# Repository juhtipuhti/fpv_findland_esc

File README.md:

# fpv_findland_esc
20x20mm mounted esc made for AM32. Currently work in progress. Confirmed to spin motors, but there are some emf problems at high output.

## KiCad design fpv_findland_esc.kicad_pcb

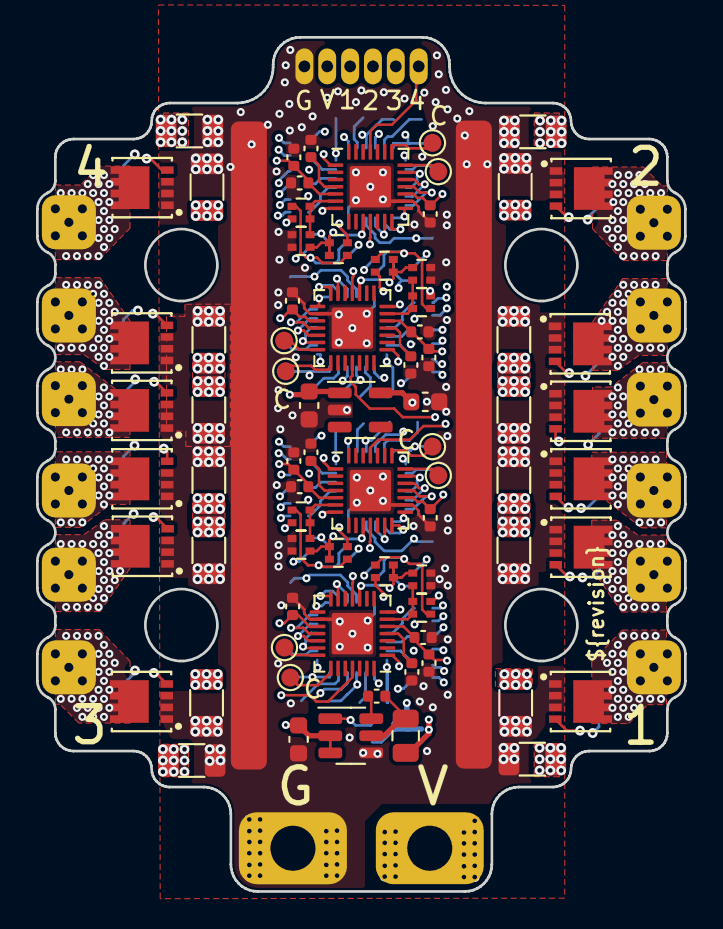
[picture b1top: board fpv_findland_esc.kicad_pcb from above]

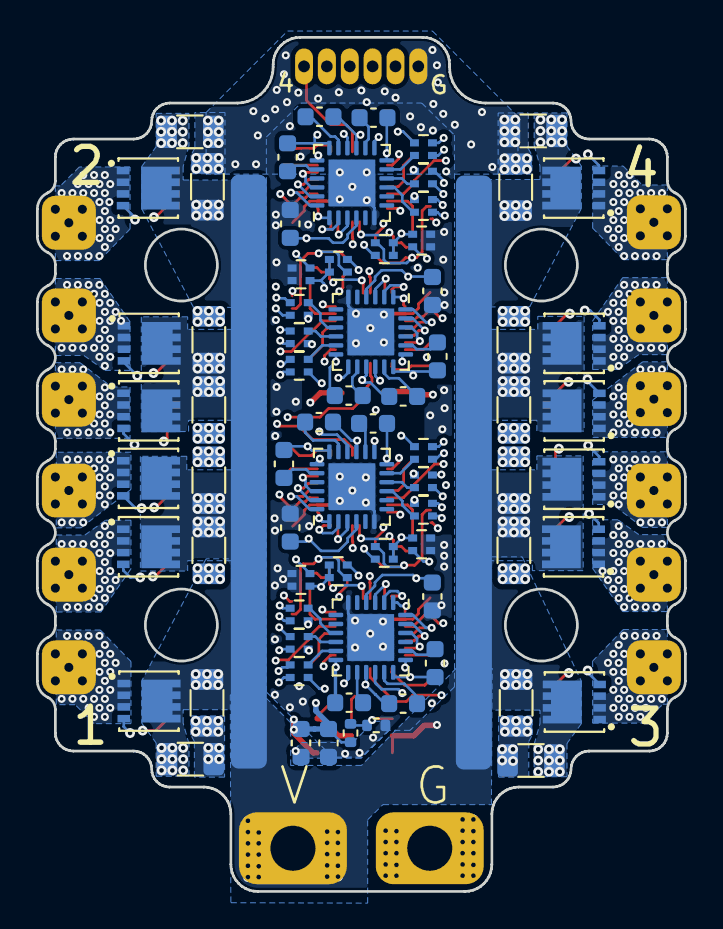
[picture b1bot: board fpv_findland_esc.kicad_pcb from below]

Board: 6 copper layers, 36.0 x 47.4 mm, 166 parts (74 on the bottom side), 139 nets.

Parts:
C1, C2, C6, C7, C8, C10, C11, C16, C24, C25, C26, C27, C29, C30, C31, C32, C33, C34, C35, C37, C39, C40, C41, C42, C43, C44, C47, C53, C60, C61, C63, C64: 10uF X7R; C_1206_Slim
C3, C4, C5, C12, C13, C14, C15, C19, C20, C21, C23, C28, C65: 100nF; C_0402_1005Metric
C9, C18, C69, C70: 1uF; C_0402_1005Metric
C17, C22, C38, C52, C59, C62, C66, C67, C68: 10uF; C_0603_1608Metric
C36, C45, C46, C48, C49, C50, C51, C54, C55, C56, C57, C58: 1uF; C_0603_1608Metric
J1, J3, J4, J5, J6, J7, J8, J9, J10, J11, J12, J13: Conn_01x01_Pin; MotorPad
J2: Conn_01x06; PadsHole_1x06_P1.27mm
L1: 10uF; C_0805_2012Metric
Q1, Q2, Q3, Q4, Q5, Q6, Q7, Q8, Q9, Q10, Q11, Q12, Q13, Q14, Q15, Q16, Q17, Q18, Q19, Q20, Q21, Q22, Q23, Q24: FDMC8010DC; TRANS_FDMC8010DC
R1: 20K; R_0402_1005Metric
R2: 230K; R_0402_1005Metric
RN1, RN2, RN3, RN4, RN5, RN6, RN7, RN8, RN9, RN10, RN11, RN12, RN13, RN14, RN15, RN16, RN20, RN22, RN24, RN25: 10K; R_Array_Slim_2x0402
RN17, RN18, RN19, RN21, RN23, RN26, RN27, RN28, RN29, RN30, RN31, RN32: 22R; R_Array_Slim_2x0402
TP1, TP2, TP3, TP5, TP6, TP7, TP8, TP10: TestPoint; TestPoint_Pad_D1.0mm
TP4, TP9: BussBar; 2mmBussBar36MM
TP11, TP12: BatteryPad
TP13, TP14: BussBar; 2mmBussBar33MM
U1, U3, U4, U6: GD32E230G8U6; QFN-28-1EP_4x4mm_P0.4mm_EP2.6x2.6mm
U2: WL2851E33; SOT-23-5
U5: AP63200; SOT-23-6
U7, U8, U9, U10: DRV8300D; QFN-24-1EP_4x4mm_P0.5mm_EP2.6x2.6mm

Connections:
/3.3V: C3.1, C5.1, C9.1, C12.1, C13.1, C14.1, C15.1, C18.1, C22.1, C23.1, C28.1, C69.1, C70.1, U1.5 (VDDA), U1.17 (VDD), U2.5 (VOUT), U3.5 (VDDA), U3.17 (VDD), U4.5 (VDDA), U4.17 (VDD), U6.5 (VDDA), U6.17 (VDD)
/5V: C17.1, C38.1, C52.1, C59.1, C62.1, C66.1, C67.1, L1.2, R2.1, U2.1 (VIN), U7.4 (VDD), U8.4 (VDD), U9.4 (VDD), U10.4 (VDD)
/ESC1/AHIGH: U4.20 (PA10), U8.22 (INHA)
/ESC1/ALOW: U4.15 (PB1), U8.1 (INLA)
/ESC1/BEMFA_1: RN8.1 (R1.1), RN8.2 (R2.1), RN11.2 (R2.1), U4.6 (PA0)
/ESC1/BEMFB_1: RN9.1 (R1.1), RN9.2 (R2.1), RN11.1 (R1.1), U4.10 (PA4)
/ESC1/BEMFC_1: RN7.1 (R1.1), RN7.2 (R2.1), RN10.1 (R1.1), U4.11 (PA5)
/ESC1/BEMF_COMMON: RN7.3 (R2.2), RN8.3 (R2.2), RN9.3 (R2.2), U4.7 (PA1)
/ESC1/BHIGH: U4.19 (PA9), U8.23 (INHB)
/ESC1/BLOW: U4.14 (PB0), U8.2 (INLB)
/ESC1/Boot0: RN10.2 (R2.1), U4.1 (BOOT0)
/ESC1/CHIGH: U4.18 (PA8), U8.24 (INHC)
/ESC1/CLOW: U4.13 (PA7), U8.3 (INLC)
/ESC1/GHA: RN21.3 (R2.2), U8.19 (GHA)
/ESC1/GHB: RN28.3 (R2.2), U8.16 (GHB)
/ESC1/GHC: RN32.3 (R2.2), U8.13 (GHC)
/ESC1/GLA: RN21.4 (R1.2), U8.11 (GLA)
/ESC1/GLB: RN28.4 (R1.2), U8.10 (GLB)
/ESC1/GLC: RN32.4 (R1.2), U8.9 (GLC)
/ESC1/MotorOutA: C55.1, J12.1, Q12.5 (D), Q23.1 (S), Q23.2 (S), Q23.3 (S), RN8.4 (R1.2), U8.18 (SHA)
/ESC1/MotorOutB: C50.1, J13.1, Q9.5 (D), Q18.1 (S), Q18.2 (S), Q18.3 (S), RN9.4 (R1.2), U8.15 (SHB)
/ESC1/MotorOutC: C58.1, J11.1, Q8.5 (D), Q15.1 (S), Q15.2 (S), Q15.3 (S), RN7.4 (R1.2), U8.12 (SHC)
/ESC1/SWC: TP5.1, U4.22 (PA14)
/ESC1/SWD: TP7.1, U4.21 (PA13)
/ESC2/AHIGH: U1.20 (PA10), U7.22 (INHA)
/ESC2/ALOW: U1.15 (PB1), U7.1 (INLA)
/ESC2/BEMFA_1: RN2.2 (R2.1), RN5.1 (R1.1), RN5.2 (R2.1), U1.6 (PA0)
/ESC2/BEMFB_1: RN1.1 (R1.1), RN1.2 (R2.1), RN2.1 (R1.1), U1.10 (PA4)
/ESC2/BEMFC_1: RN3.1 (R1.1), RN4.1 (R1.1), RN4.2 (R2.1), U1.11 (PA5)
/ESC2/BEMF_COMMON: RN1.3 (R2.2), RN4.3 (R2.2), RN5.3 (R2.2), U1.7 (PA1)
/ESC2/BHIGH: U1.19 (PA9), U7.23 (INHB)
/ESC2/BLOW: U1.14 (PB0), U7.2 (INLB)
/ESC2/Boot0: RN3.2 (R2.1), U1.1 (BOOT0)
/ESC2/CHIGH: U1.18 (PA8), U7.24 (INHC)
/ESC2/CLOW: U1.13 (PA7), U7.3 (INLC)
/ESC2/GHA: RN19.3 (R2.2), U7.19 (GHA)
/ESC2/GHB: RN18.3 (R2.2), U7.16 (GHB)
/ESC2/GHC: RN17.3 (R2.2), U7.13 (GHC)
/ESC2/GLA: RN19.4 (R1.2), U7.11 (GLA)
/ESC2/GLB: RN18.4 (R1.2), U7.10 (GLB)
/ESC2/GLC: RN17.4 (R1.2), U7.9 (GLC)
/ESC2/MotorOutA: C36.1, J9.1, Q7.5 (D), Q17.1 (S), Q17.2 (S), Q17.3 (S), RN5.4 (R1.2), U7.18 (SHA)
/ESC2/MotorOutB: C46.1, J10.1, Q10.5 (D), Q16.1 (S), Q16.2 (S), Q16.3 (S), RN1.4 (R1.2), U7.15 (SHB)
/ESC2/MotorOutC: C56.1, J3.1, Q2.5 (D), Q13.1 (S), Q13.2 (S), Q13.3 (S), RN4.4 (R1.2), U7.12 (SHC)
/ESC2/SWC: TP3.1, U1.22 (PA14)
/ESC2/SWD: TP1.1, U1.21 (PA13)
/ESC3/AHIGH: U3.20 (PA10), U9.22 (INHA)
/ESC3/ALOW: U3.15 (PB1), U9.1 (INLA)
/ESC3/BEMFA_1: RN13.2 (R2.1), RN14.1 (R1.1), RN14.2 (R2.1), U3.6 (PA0)
/ESC3/BEMFB_1: RN13.1 (R1.1), RN15.1 (R1.1), RN15.2 (R2.1), U3.10 (PA4)
/ESC3/BEMFC_1: RN12.1 (R1.1), RN16.1 (R1.1), RN16.2 (R2.1), U3.11 (PA5)
/ESC3/BEMF_COMMON: RN14.3 (R2.2), RN15.3 (R2.2), RN16.3 (R2.2), U3.7 (PA1)
/ESC3/BHIGH: U3.19 (PA9), U9.23 (INHB)
/ESC3/BLOW: U3.14 (PB0), U9.2 (INLB)
/ESC3/Boot0: RN12.2 (R2.1), U3.1 (BOOT0)
/ESC3/CHIGH: U3.18 (PA8), U9.24 (INHC)
/ESC3/CLOW: U3.13 (PA7), U9.3 (INLC)
/ESC3/GHA: RN30.3 (R2.2), U9.19 (GHA)
/ESC3/GHB: RN27.3 (R2.2), U9.16 (GHB)
/ESC3/GHC: RN31.3 (R2.2), U9.13 (GHC)
/ESC3/GLA: RN30.4 (R1.2), U9.11 (GLA)
/ESC3/GLB: RN27.4 (R1.2), U9.10 (GLB)
/ESC3/GLC: RN31.4 (R1.2), U9.9 (GLC)
/ESC3/MotorOutA: C45.1, J7.1, Q6.5 (D), Q21.1 (S), Q21.2 (S), Q21.3 (S), RN14.4 (R1.2), U9.18 (SHA)
/ESC3/MotorOutB: C57.1, J8.1, Q5.5 (D), Q22.1 (S), Q22.2 (S), Q22.3 (S), RN15.4 (R1.2), U9.15 (SHB)
/ESC3/MotorOutC: C48.1, J5.1, Q11.5 (D), Q24.1 (S), Q24.2 (S), Q24.3 (S), RN16.4 (R1.2), U9.12 (SHC)
/ESC3/SWC: TP10.1, U3.22 (PA14)
/ESC3/SWD: TP8.1, U3.21 (PA13)
/ESC4/AHIGH: U6.20 (PA10), U10.22 (INHA)
/ESC4/ALOW: U6.15 (PB1), U10.1 (INLA)
/ESC4/BEMFA_1: RN6.1 (R1.1), RN6.2 (R2.1), RN22.2 (R2.1), U6.6 (PA0)
/ESC4/BEMFB_1: RN20.1 (R1.1), RN20.2 (R2.1), RN22.1 (R1.1), U6.10 (PA4)
/ESC4/BEMFC_1: RN24.1 (R1.1), RN25.1 (R1.1), RN25.2 (R2.1), U6.11 (PA5)
/ESC4/BEMF_COMMON: RN6.3 (R2.2), RN20.3 (R2.2), RN25.3 (R2.2), U6.7 (PA1)
/ESC4/BHIGH: U6.19 (PA9), U10.23 (INHB)
/ESC4/BLOW: U6.14 (PB0), U10.2 (INLB)
/ESC4/Boot0: RN24.2 (R2.1), U6.1 (BOOT0)
/ESC4/CHIGH: U6.18 (PA8), U10.24 (INHC)
/ESC4/CLOW: U6.13 (PA7), U10.3 (INLC)
/ESC4/GHA: RN26.3 (R2.2), U10.19 (GHA)
/ESC4/GHB: RN23.3 (R2.2), U10.16 (GHB)
/ESC4/GHC: RN29.3 (R2.2), U10.13 (GHC)
/ESC4/GLA: RN26.4 (R1.2), U10.11 (GLA)
/ESC4/GLB: RN23.4 (R1.2), U10.10 (GLB)
/ESC4/GLC: RN29.4 (R1.2), U10.9 (GLC)
/ESC4/MotorOutA: C49.1, J1.1, Q1.5 (D), Q14.1 (S), Q14.2 (S), Q14.3 (S), RN6.4 (R1.2), U10.18 (SHA)
/ESC4/MotorOutB: C54.1, J6.1, Q4.5 (D), Q20.1 (S), Q20.2 (S), Q20.3 (S), RN20.4 (R1.2), U10.15 (SHB)
/ESC4/MotorOutC: C51.1, J4.1, Q3.5 (D), Q19.1 (S), Q19.2 (S), Q19.3 (S), RN25.4 (R1.2), U10.12 (SHC)
/ESC4/SWC: TP6.1, U6.22 (PA14)
/ESC4/SWD: TP2.1, U6.21 (PA13)
/M1: J2.4, U4.25 (PB4)
/M2: J2.3, U1.25 (PB4)
/M3: J2.2, U3.25 (PB4)
/M4: J2.1, U6.25 (PB4)
/VBAT: C1.1, C2.1, C6.1, C7.1, C8.1, C10.1, C11.1, C16.1, C24.1, C25.1, C26.1, C27.1, C29.1, C30.1, C31.1, C32.1, C33.1, C34.1, C35.1, C37.1, C39.1, C40.1, C41.1, C42.1, C43.1, C44.1, C47.1, C53.1, C60.1, C61.1, C63.1, C64.1, C68.1, J2.5, Q13.5 (D), Q14.5 (D), Q15.5 (D), Q16.5 (D), Q17.5 (D), Q18.5 (D), Q19.5 (D), Q20.5 (D), Q21.5 (D), Q22.5 (D), Q23.5 (D), Q24.5 (D), TP12.1, TP13.1, TP14.1, U5.2 (EN), U5.3 (VIN)
GND: C1.2, C2.2, C3.2, C4.2, C5.2, C6.2, C7.2, C8.2, C9.2, C10.2, C11.2, C12.2, C13.2, C14.2, C15.2, C16.2, C17.2, C18.2, C19.2, C20.2, C21.2, C22.2, C23.2, C24.2, C25.2, C26.2, C27.2, C28.2, C29.2, C30.2, C31.2, C32.2, C33.2, C34.2, C35.2, C37.2, C38.2, C39.2, C40.2, C41.2, C42.2, C43.2, C44.2, C47.2, C52.2, C53.2, C59.2, C60.2, C61.2, C62.2, C63.2, C64.2, C66.2, C67.2, C68.2, C69.2, C70.2, J2.6, Q1.1 (S), Q1.2 (S), Q1.3 (S), Q2.1 (S), Q2.2 (S), Q2.3 (S), Q3.1 (S), Q3.2 (S), Q3.3 (S), Q4.1 (S), Q4.2 (S), Q4.3 (S), Q5.1 (S), Q5.2 (S), Q5.3 (S), Q6.1 (S), Q6.2 (S), Q6.3 (S), Q7.1 (S), Q7.2 (S), Q7.3 (S), Q8.1 (S), Q8.2 (S), Q8.3 (S), Q9.1 (S), Q9.2 (S), Q9.3 (S), Q10.1 (S), Q10.2 (S), Q10.3 (S), Q11.1 (S), Q11.2 (S), Q11.3 (S), Q12.1 (S), Q12.2 (S), Q12.3 (S), R1.2, RN2.3 (R2.2), RN2.4 (R1.2), RN3.3 (R2.2), RN3.4 (R1.2), RN10.3 (R2.2), RN10.4 (R1.2), RN11.3 (R2.2), RN11.4 (R1.2), RN12.3 (R2.2), RN12.4 (R1.2), RN13.3 (R2.2), RN13.4 (R1.2), RN22.3 (R2.2), RN22.4 (R1.2), RN24.3 (R2.2), RN24.4 (R1.2), TP4.1, TP9.1, TP11.1, U1.16 (VSS), U1.29 (VSS), U2.2 (GND), U3.16 (VSS), U3.29 (VSS), U4.16 (VSS), U4.29 (VSS), U5.4 (GND), U6.16 (VSS), U6.29 (VSS), U7.6 (GND), U7.25 (GND), U8.6 (GND), U8.25 (GND), U9.6 (GND), U9.25 (GND), U10.6 (GND), U10.25 (GND)
unnamed: Q1.4 (G), RN26.1 (R1.1)
unnamed: Q2.4 (G), RN17.1 (R1.1)
unnamed: Q3.4 (G), RN29.1 (R1.1)
unnamed: Q4.4 (G), RN23.1 (R1.1)
unnamed: Q5.4 (G), RN27.1 (R1.1)
unnamed: Q6.4 (G), RN30.1 (R1.1)
unnamed: Q7.4 (G), RN19.1 (R1.1)
unnamed: Q8.4 (G), RN32.1 (R1.1)
unnamed: Q9.4 (G), RN28.1 (R1.1)
unnamed: Q10.4 (G), RN18.1 (R1.1)
unnamed: Q11.4 (G), RN31.1 (R1.1)
unnamed: Q12.4 (G), RN21.1 (R1.1)
unnamed: Q13.4 (G), RN17.2 (R2.1)
unnamed: Q14.4 (G), RN26.2 (R2.1)
unnamed: Q15.4 (G), RN32.2 (R2.1)
unnamed: Q16.4 (G), RN18.2 (R2.1)
unnamed: Q17.4 (G), RN19.2 (R2.1)
unnamed: Q18.4 (G), RN28.2 (R2.1)
unnamed: Q19.4 (G), RN29.2 (R2.1)
unnamed: Q20.4 (G), RN23.2 (R2.1)
unnamed: Q21.4 (G), RN30.2 (R2.1)
unnamed: Q22.4 (G), RN27.2 (R2.1)
unnamed: Q23.4 (G), RN21.2 (R2.1)
unnamed: Q24.4 (G), RN31.2 (R2.1)
unnamed: C4.1, U1.4 (NRST)
unnamed: C21.1, U3.4 (NRST)
unnamed: C19.1, U4.4 (NRST)
unnamed: C65.2, U5.6 (BST)
unnamed: R1.1, R2.2, U5.1 (FB)
unnamed: C65.1, L1.1, U5.5 (SW)
unnamed: C20.1, U6.4 (NRST)
unnamed: C36.2, U7.20 (BSTA)
unnamed: C46.2, U7.17 (BSTB)
unnamed: C56.2, U7.14 (BSTC)
unnamed: C55.2, U8.20 (BSTA)
unnamed: C50.2, U8.17 (BSTB)
unnamed: C58.2, U8.14 (BSTC)
unnamed: C45.2, U9.20 (BSTA)
unnamed: C57.2, U9.17 (BSTB)
unnamed: C48.2, U9.14 (BSTC)
unnamed: C49.2, U10.20 (BSTA)
unnamed: C54.2, U10.17 (BSTB)
unnamed: C51.2, U10.14 (BSTC)

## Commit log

2023-05-24 Create images
2023-05-24 Create test
2023-05-25 Change name
2023-05-25 Fixed revisions
2023-05-31 Added copperfill for VBAT in layer In4. Other small fixes.
2023-05-31 Optimized layer In2 for more current.
2023-06-02 Removed gerbers
2023-06-07 Moved top layer fets to allow more current. Other small improvements.
2023-06-07 Moved motor pads to allow more current.
2024-06-30 Test
2024-06-30 Updated power supply scheme. 10V step down to a 3.3V LDO.
2024-07-03 Removed unneccessary islands etc.
2024-07-03 Removed some sharp corners etc
